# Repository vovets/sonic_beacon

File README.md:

# Sonic Beacon

## Overview
This little device is supposed to provide an aid in finding small RC models in the grass or other obstacles. It does so by emitting series of loud beeps. It was originally designed to be used with Blade series of micro helicopters but can be used with any model that has throttle signal.

## Operating conditions
| Parameter | Value(s) |
| --- | --- |
| Input Voltage | 3...16 V |
| Input Signal Type | PWM >500 Hz or Standard Servo PWM 1500 uS center, <500Hz |
| Throttle Threshold PWM | 1/8 (12.5%) duty cycle |
| Throttle Threshold Servo | 1248 uS (25% of full throttle) |
## Modes of operation
Device has two modes of operation: auxiliary "calibration" which will be discussed later and main "normal".

## Theory of operation ("normal" mode)
1. Device gets powered on and automatically detects control signal type be it standard servo signal or PWM.
1. Device waits for the control signal to be higher than threshold value for more than 3 seconds then device becomes "armed".
1. Device waits for the control signal to be lower than threshold value for more than 30 seconds then device starts emitting series of tones and does so indefinitely.

## Practice of operation ("normal" mode)
1. Operator powers up model.
1. Operator starts flying model. To do so he pushes the throttle up, so throttle gets higher than the threshold. In 3 seconds beacon arms and emits two tones.
1. In the unfortunate event that the model can not be sighted after landing because of grass or other obstacles operator zeroes the throttle (or failsafe does so). After 30 seconds beacon starts emitting beeps and that aids operator in locating model ~~crash~~landing site.

## Connections

## Tone frequency calibration ("calibration" mode)
The frequency of the tone emitted by the device can be adjusted by user to accommodate for differences in hearing or variations in device base frequency. Adjusted frequency is stored in device's eeprom so it is not lost after power off.

Device pcb has two special pads for this purpose designated as **DEC** and **INC** in schematics and silk layer.
To adjust frequency it is needed to solder buttons from these pad to **GND** pad or use piece of wire or metallic tweezers or something similar. In the following we will refer to them as buttons for brevity.

To enter calibration mode **DEC** button must be pressed upon powering device on. Device starts emitting continuous tone. Frequency of the tone can be adjusted by pressing **INC** or **DEC** buttons. Adjusted frequency gets immediately stored in the eeprom. To exit this mode device needs to be powered off.

## Good practice
It is highly recommeded that after installation on the model device undergoes full functionality test. **_Any propellers and blades must be removed from the model before starting any tests._**

## Implementation details

### Directory structure
```
.
├── doc          - schematics in pdf, images
├── board        - schematics, board, library for Eagle
│   └── output   - Eagle output: pdf, tiff, etc.
└── firmware     - software sources for IAR Embedded Workbench
    ├── Release  - compiler output, ignored by git
    │   ├── Exe  - flash.hex (flash.bin) is a file you are looking For
    │   ├── List
    │   └── Obj
    └── settings - IAR settings, ignored by git
```

### Schematics in pdf
[Here.](doc/sonic_beacon.pdf)

### Components
* MCU - ATtiny85-20, as firmware size is under 4k so ATtiny45-20 should also do. Uses 8 MHz internal RC clock which provides for stable operation at as low as 2.7V.
* Voltage Regulator - TI LP2981-33 ultra-low dropout. Provides 3-16V working voltage range.

### Fuses

```
SELFPRGEN = [ ]
RSTDISBL = [ ]
DWEN = [ ]
SPIEN = [X]
WDTON = [ ]
EESAVE = [X]
BODLEVEL = 1V8
CKDIV8 = [ ]
CKOUT = [ ]
SUT_CKSEL = INTRCOSC_8MHZ_6CK_14CK_64MS

EXTENDED = 0xFF
HIGH = 0xD6
LOW = 0xE2
```

### Places of interest in source files
1. [Where the throttle threshold is defined for PWM signal?](https://github.com/vovets/sonic_beacon/blob/433788d3e038b642e70308b3990e0a55145812b6/firmware/sonic_beacon.c#L87)
1. [Where the throttle threshold is defined for Servo signal?](https://github.com/vovets/sonic_beacon/blob/433788d3e038b642e70308b3990e0a55145812b6/firmware/signal_detection.c#L192)

### Software versions
Software versions with which board and firmware were developed.
1. Eagle 7.5 or 7.7
1. IAR Embedded Workbench 6.8

### Cheap hardware/sofware for firmware flashing
* [usbasp](http://www.fischl.de/usbasp/) - under $5 usb device for flashing AVR MCUs. Can be found on ebay, aliexpress, banggood and even hobbyking. 
* [avrdude](https://www.nongnu.org/avrdude/) - command line software for flashing AVR MCUs. There are versions for Windows and GUI tools available.

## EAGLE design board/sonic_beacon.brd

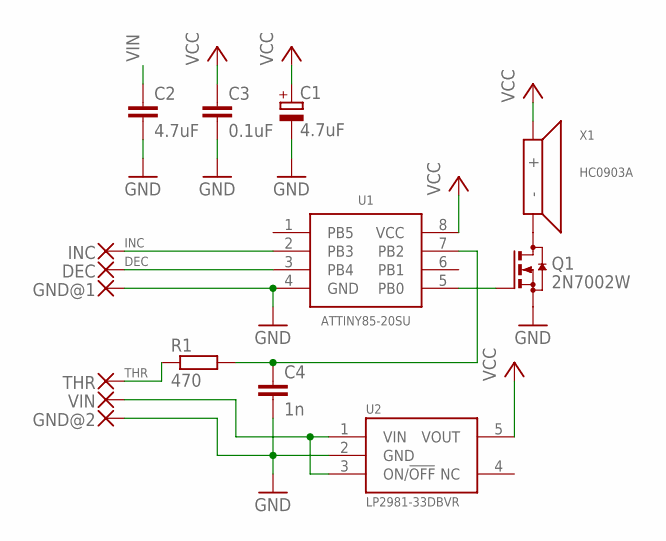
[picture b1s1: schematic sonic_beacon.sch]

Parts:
C1: 4.7uF; A/3216-18W
C2: 4.7uF; C0805K
C3: 0.1uF; C0805K
C4: 1n; C0805K
DEC: WIREPAD; PAD
GND@1, GND@2: WIREPAD; PAD
INC: WIREPAD; PAD
Q1: 2N7002W; SC-70
R1: 470; R0805W
THR: WIREPAD; PAD
U1: ATTINY85-20SU; 8S2
U2: LP2981-33DBVR; SOT-23
VIN: WIREPAD; PAD
X1: HC0903A

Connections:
DEC: DEC.P$1, U1.3 (PB4)
GND: C1.-, C2.2, C3.2, C4.2, GND@1.P$1, GND@2.P$1, Q1.2 (S), U1.4 (GND), U2.2 (GND)
INC: INC.P$1, U1.2 (PB3)
unnamed: Q1.1 (G), U1.5 (PB0)
unnamed: Q1.3 (D), X1.2 (-)
unnamed: U2.1 (VIN), U2.3 (ON/!OFF), VIN.P$1
unnamed: C4.1, R1.2, U1.7 (PB2)
THR: R1.1, THR.P$1
VCC: C1.+, C3.1, U1.8 (VCC), U2.5 (VOUT), X1.1 (+)
VIN: C2.1

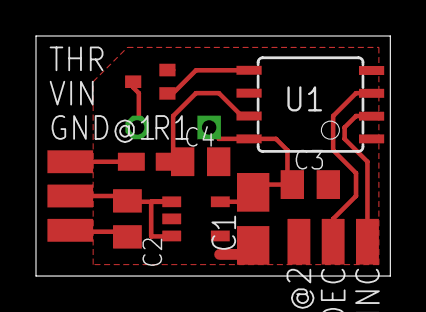
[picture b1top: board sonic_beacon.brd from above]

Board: 2 copper layers, 19.7 x 13.3 mm, 15 parts (1 on the bottom side), 9 nets.

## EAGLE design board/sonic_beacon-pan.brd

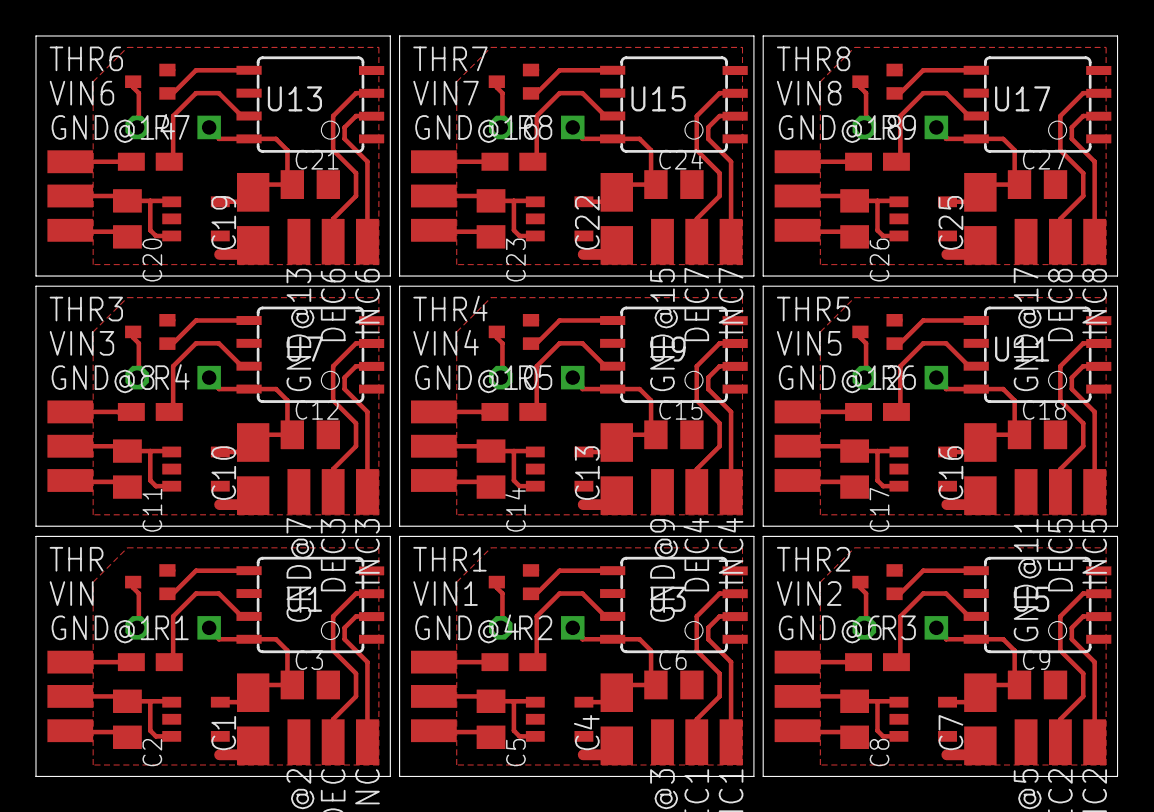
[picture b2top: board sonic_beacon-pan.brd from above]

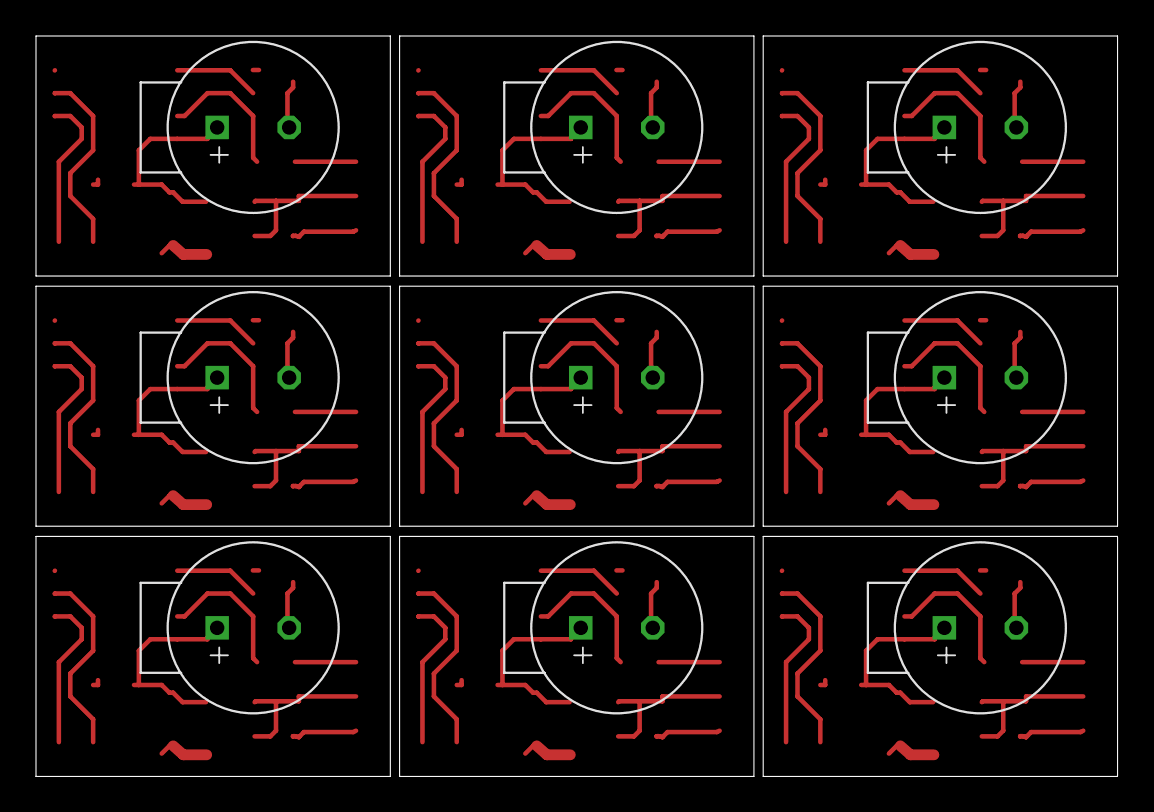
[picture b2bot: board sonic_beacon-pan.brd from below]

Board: 2 copper layers, 60.1 x 41.1 mm, 126 parts (9 on the bottom side), 81 nets.

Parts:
C1, C4, C7, C10, C13, C16, C19, C22, C25: 4.7uF; A/3216-18W
C2, C5, C8, C11, C14, C17, C20, C23, C26: 4.7uF; C0805K
C3, C6, C9, C12, C15, C18, C21, C24, C27: 0.1uF; C0805K
DEC, DEC1, DEC2, DEC3, DEC4, DEC5, DEC6, DEC7, DEC8: PAD
GND@1, GND@2, GND@3, GND@4, GND@5, GND@6, GND@7, GND@8, GND@9, GND@10, GND@11, GND@12, GND@13, GND@14, GND@15, GND@16, GND@17, GND@18: PAD
INC, INC1, INC2, INC3, INC4, INC5, INC6, INC7, INC8: PAD
Q1, Q2, Q3, Q4, Q5, Q6, Q7, Q8, Q9: 2N7002W; SC-70
R1, R2, R3, R4, R5, R6, R7, R8, R9: 100; R0805W
THR, THR1, THR2, THR3, THR4, THR5, THR6, THR7, THR8: PAD
U1, U3, U5, U7, U9, U11, U13, U15, U17: ATTINY85-20SU; 8S2
U2, U4, U6, U8, U10, U12, U14, U16, U18: LP2981-33DBVR; SOT-23
VIN, VIN1, VIN2, VIN3, VIN4, VIN5, VIN6, VIN7, VIN8: PAD
X1, X2, X3, X4, X5, X6, X7, X8, X9: HC0903A

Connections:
DEC: DEC.P$1, U1.3
DEC1: DEC1.P$1, U3.3
DEC2: DEC2.P$1, U5.3
DEC3: DEC3.P$1, U7.3
DEC4: DEC4.P$1, U9.3
DEC5: DEC5.P$1, U11.3
DEC6: DEC6.P$1, U13.3
DEC7: DEC7.P$1, U15.3
DEC8: DEC8.P$1, U17.3
GND: C1.-, C2.2, C3.2, GND@1.P$1, GND@2.P$1, Q1.2, U1.4, U2.2
GND1: C4.-, C5.2, C6.2, GND@3.P$1, GND@4.P$1, Q2.2, U3.4, U4.2
GND2: C7.-, C8.2, C9.2, GND@5.P$1, GND@6.P$1, Q3.2, U5.4, U6.2
GND3: C10.-, C11.2, C12.2, GND@7.P$1, GND@8.P$1, Q4.2, U7.4, U8.2
GND4: C13.-, C14.2, C15.2, GND@9.P$1, GND@10.P$1, Q5.2, U9.4, U10.2
GND5: C16.-, C17.2, C18.2, GND@11.P$1, GND@12.P$1, Q6.2, U11.4, U12.2
GND6: C19.-, C20.2, C21.2, GND@13.P$1, GND@14.P$1, Q7.2, U13.4, U14.2
GND7: C22.-, C23.2, C24.2, GND@15.P$1, GND@16.P$1, Q8.2, U15.4, U16.2
GND8: C25.-, C26.2, C27.2, GND@17.P$1, GND@18.P$1, Q9.2, U17.4, U18.2
INC: INC.P$1, U1.2
INC1: INC1.P$1, U3.2
INC2: INC2.P$1, U5.2
INC3: INC3.P$1, U7.2
INC4: INC4.P$1, U9.2
INC5: INC5.P$1, U11.2
INC6: INC6.P$1, U13.2
INC7: INC7.P$1, U15.2
INC8: INC8.P$1, U17.2
unnamed: Q1.1, U1.5
unnamed: Q1.3, X1.2
unnamed: Q2.1, U3.5
unnamed: R1.2, U1.7
unnamed: Q2.3, X2.2
unnamed: R2.2, U3.7
unnamed: Q3.1, U5.5
unnamed: Q3.3, X3.2
unnamed: R3.2, U5.7
unnamed: Q4.1, U7.5
unnamed: Q4.3, X4.2
unnamed: R4.2, U7.7
unnamed: Q5.1, U9.5
unnamed: Q5.3, X5.2
unnamed: R5.2, U9.7
unnamed: Q6.1, U11.5
unnamed: Q6.3, X6.2
unnamed: R6.2, U11.7
unnamed: Q7.1, U13.5
unnamed: Q7.3, X7.2
unnamed: R7.2, U13.7
unnamed: Q8.1, U15.5
unnamed: Q8.3, X8.2
unnamed: R8.2, U15.7
unnamed: Q9.1, U17.5
unnamed: Q9.3, X9.2
unnamed: R9.2, U17.7
THR: R1.1, THR.P$1
THR1: R2.1, THR1.P$1
THR2: R3.1, THR2.P$1
THR3: R4.1, THR3.P$1
THR4: R5.1, THR4.P$1
THR5: R6.1, THR5.P$1
THR6: R7.1, THR6.P$1
THR7: R8.1, THR7.P$1
THR8: R9.1, THR8.P$1
VCC: C1.+, C3.1, U1.8, U2.5, X1.1
VCC1: C4.+, C6.1, U3.8, U4.5, X2.1
VCC2: C7.+, C9.1, U5.8, U6.5, X3.1
VCC3: C10.+, C12.1, U7.8, U8.5, X4.1
VCC4: C13.+, C15.1, U9.8, U10.5, X5.1
VCC5: C16.+, C18.1, U11.8, U12.5, X6.1
VCC6: C19.+, C21.1, U13.8, U14.5, X7.1
VCC7: C22.+, C24.1, U15.8, U16.5, X8.1
VCC8: C25.+, C27.1, U17.8, U18.5, X9.1
VIN: C2.1, U2.1, U2.3, VIN.P$1
VIN1: C5.1, U4.1, U4.3, VIN1.P$1
VIN2: C8.1, U6.1, U6.3, VIN2.P$1
VIN3: C11.1, U8.1, U8.3, VIN3.P$1
VIN4: C14.1, U10.1, U10.3, VIN4.P$1
VIN5: C17.1, U12.1, U12.3, VIN5.P$1
VIN6: C20.1, U14.1, U14.3, VIN6.P$1
VIN7: C23.1, U16.1, U16.3, VIN7.P$1
VIN8: C26.1, U18.1, U18.3, VIN8.P$1

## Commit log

2018-03-24 added .gitignore to ignore settings/* Debug/* Release/*
2018-03-24 don't track settings dir
2018-03-24 converted projects to IAR 6.80.6
2018-03-24 removed obsolete "frequency_tuner" project along with associated sources
2018-03-24 removed *.dep and added to .gitignore
2018-03-25 Create README.md
    Added basic description, more to follow...
2018-03-26 Added fuse values
2018-03-26 generate raw bin output file
2018-03-26 moved firmware sources to separate dir
2018-03-26 deleted and ignored eagle backup files
2018-03-27 deleted datasheet for lp2981
2018-03-27 added connection diagram, schematics in pdf
2018-03-27 ignore eagle lock files
2018-03-27 link to schematics in pdf
2018-03-27 aded note about testing
2018-03-27 added links to where throttle threshold defined in sources
2018-03-28 Added software versions and avrdude/usbasp links
